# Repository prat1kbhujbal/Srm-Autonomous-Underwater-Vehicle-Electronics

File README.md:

Srm-Autonomous-Underwater-Vehicle-Electronics

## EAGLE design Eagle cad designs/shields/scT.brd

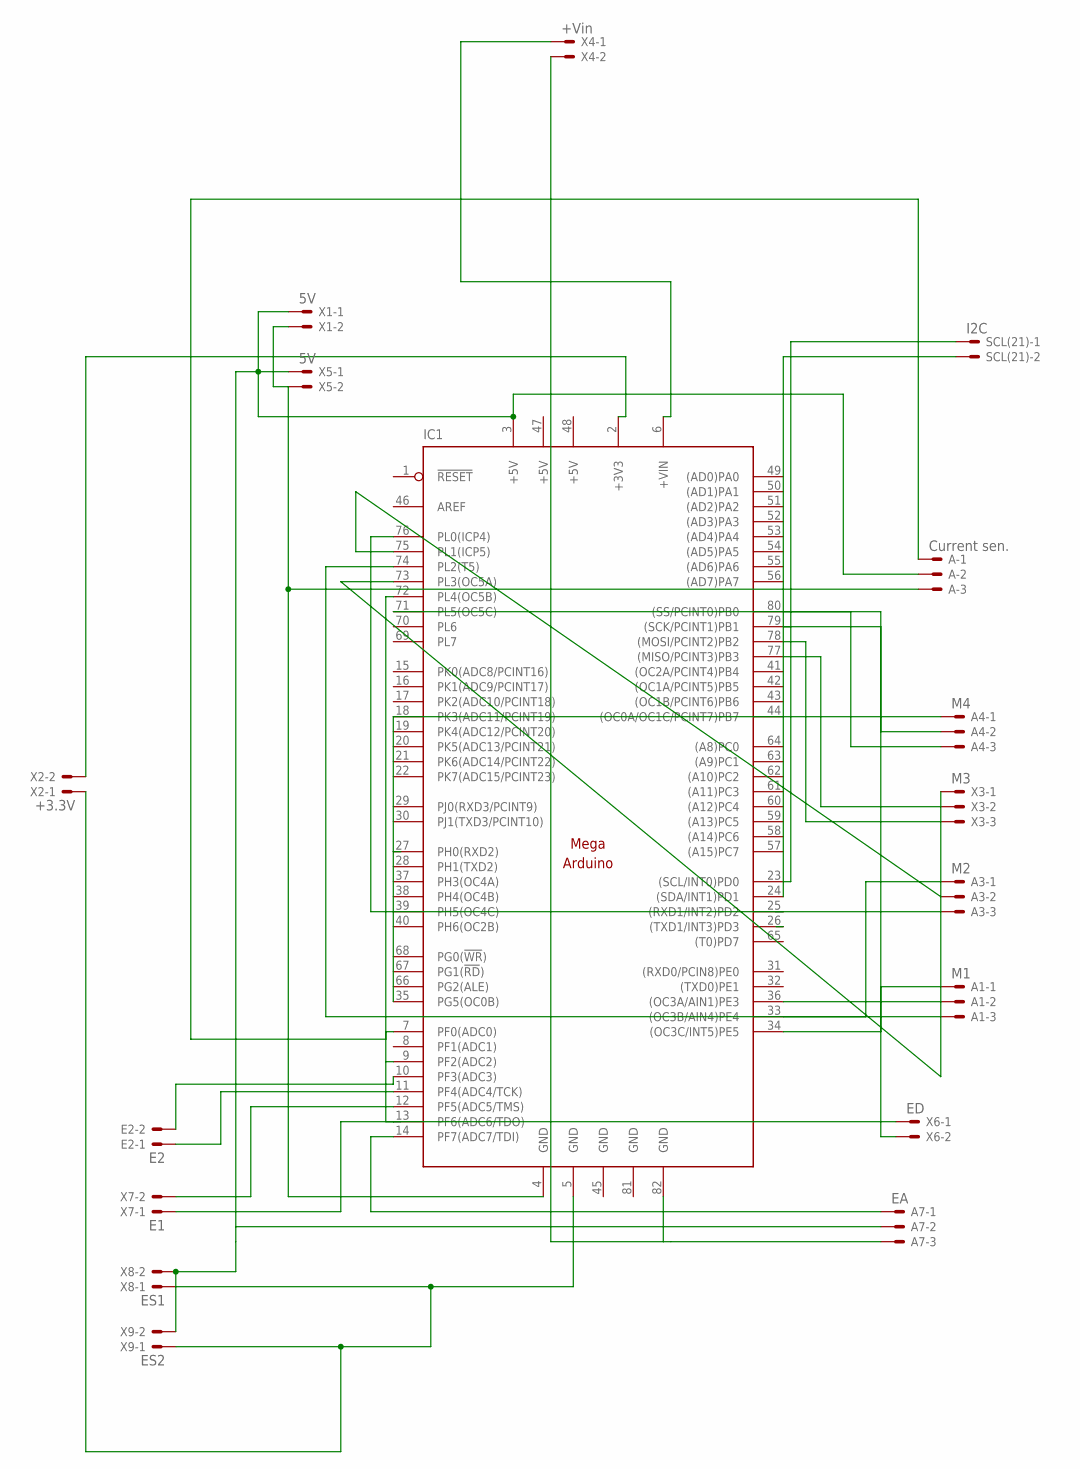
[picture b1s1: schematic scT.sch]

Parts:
A: Current sen.; JST-XH-03-PACKAGE-LONG-PAD
A1: M1; JST-XH-03-PACKAGE-LONG-PAD
A3: M2; JST-XH-03-PACKAGE-LONG-PAD
A4: M4; JST-XH-03-PACKAGE-LONG-PAD
A7: EA; JST-XH-03-PACKAGE-LONG-PAD
E2: E2; JST-XH-02-PACKAGE-LONG-PAD
IC1: MEGAARDUINO_11; MEGA_ARDUINO_1
SCL(21): I2C; JST-XH-02-PACKAGE-LONG-PAD
X1, X5: 5V; JST-XH-02-PACKAGE-LONG-PAD
X2: +3.3V; JST-XH-02-PACKAGE-LONG-PAD
X3: M3; JST-XH-03-PACKAGE-LONG-PAD
X4: +Vin; JST-XH-02-PACKAGE-LONG-PAD
X6: ED; JST-XH-02-PACKAGE-LONG-PAD
X7: E1; JST-XH-02-PACKAGE-LONG-PAD
X8: ES1; JST-XH-02-PACKAGE-LONG-PAD
X9: ES2; JST-XH-02-PACKAGE-LONG-PAD

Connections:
+5V: IC1.47 (+5V), IC1.48 (+5V)
GND: IC1.45 (GND), IC1.81 (GND)
unnamed: IC1.12 (PF5(ADC5/TMS)), X7.2
unnamed: A4.1, IC1.35 (PG5(OC0B))
unnamed: A4.2, IC1.79 ((SCK/PCINT1)PB1)
unnamed: IC1.36 ((OC3A/AIN1)PE3), X3.1
unnamed: A3.2, IC1.75 (PL1(ICP5))
unnamed: A3.1, IC1.33 ((OC3B/AIN4)PE4)
unnamed: A1.1, IC1.34 ((OC3C/INT5)PE5)
unnamed: IC1.77 ((MISO/PCINT3)PB3), X3.2
unnamed: A3.3, IC1.76 (PL0(ICP4))
unnamed: IC1.2 (+3V3), X2.2
unnamed: A.1, IC1.7 (PF0(ADC0))
unnamed: A.3, IC1.4 (GND), X1.2, X5.2
unnamed: A4.3, IC1.80 ((SS/PCINT0)PB0)
unnamed: E2.2, IC1.10 (PF3(ADC3))
unnamed: E2.1, IC1.11 (PF4(ADC4/TCK))
unnamed: IC1.78 ((MOSI/PCINT2)PB2), X3.3
unnamed: IC1.13 (PF6(ADC6/TDO)), X7.1
unnamed: A1.2, IC1.73 (PL3(OC5A))
unnamed: A1.3, IC1.74 (PL2(T5))
unnamed: IC1.5 (GND), X2.1, X8.1, X9.1
unnamed: A.2, A7.2, IC1.3 (+5V), X1.1, X5.1, X8.2, X9.2
unnamed: IC1.72 (PL4(OC5B)), X6.1
unnamed: IC1.71 (PL5(OC5C)), X6.2
unnamed: A7.1, IC1.14 (PF7(ADC7/TDI))
unnamed: A7.3, IC1.82 (GND), X4.2
unnamed: IC1.23 ((SCL/INT0)PD0), SCL(21).1
unnamed: IC1.24 ((SDA/INT1)PD1), SCL(21).2
unnamed: IC1.6 (+VIN), X4.1

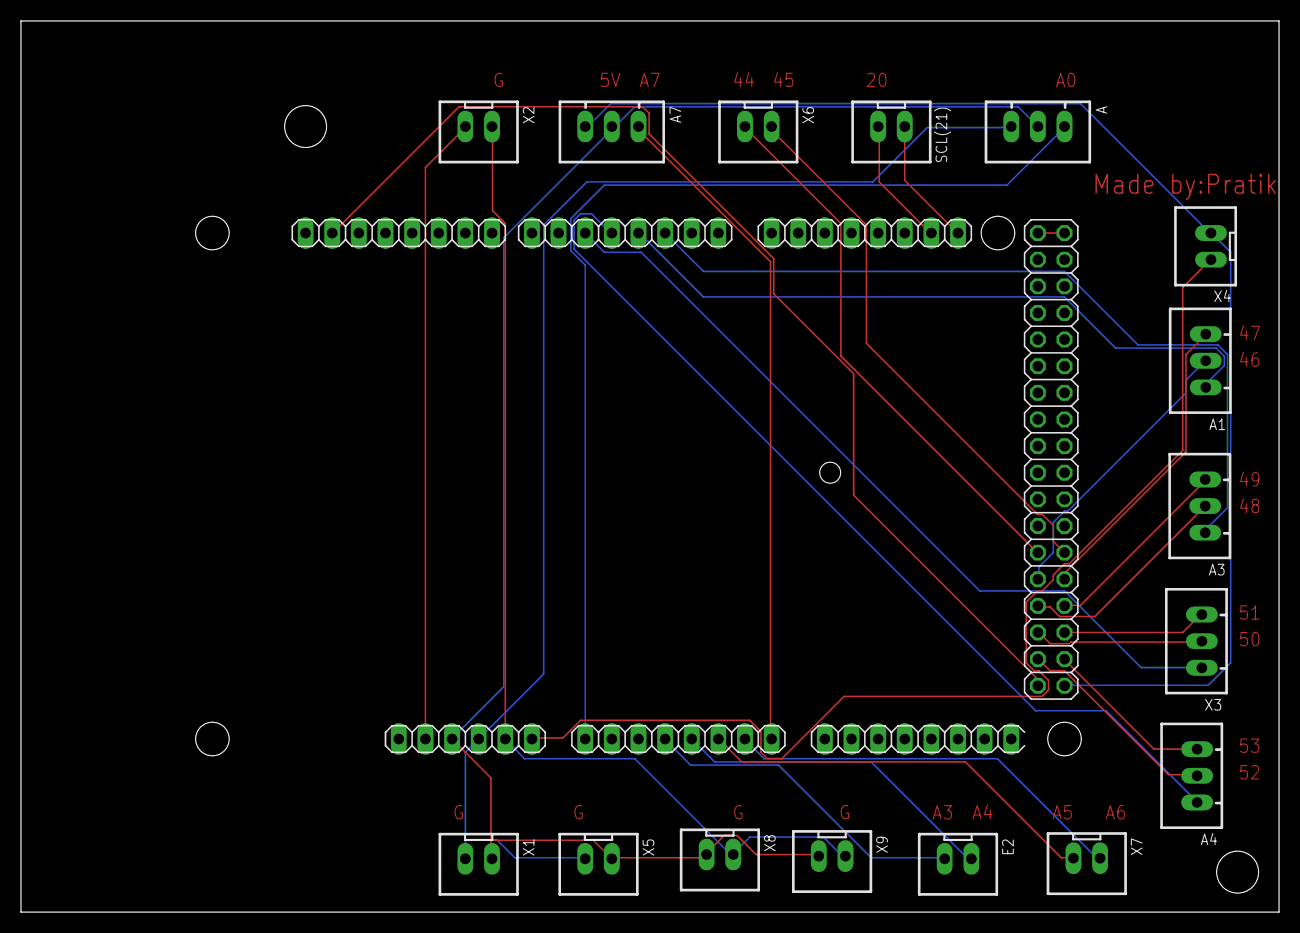
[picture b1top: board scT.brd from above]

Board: 2 copper layers, 120.0 x 85.0 mm, 17 parts (0 on the bottom side), 30 nets.

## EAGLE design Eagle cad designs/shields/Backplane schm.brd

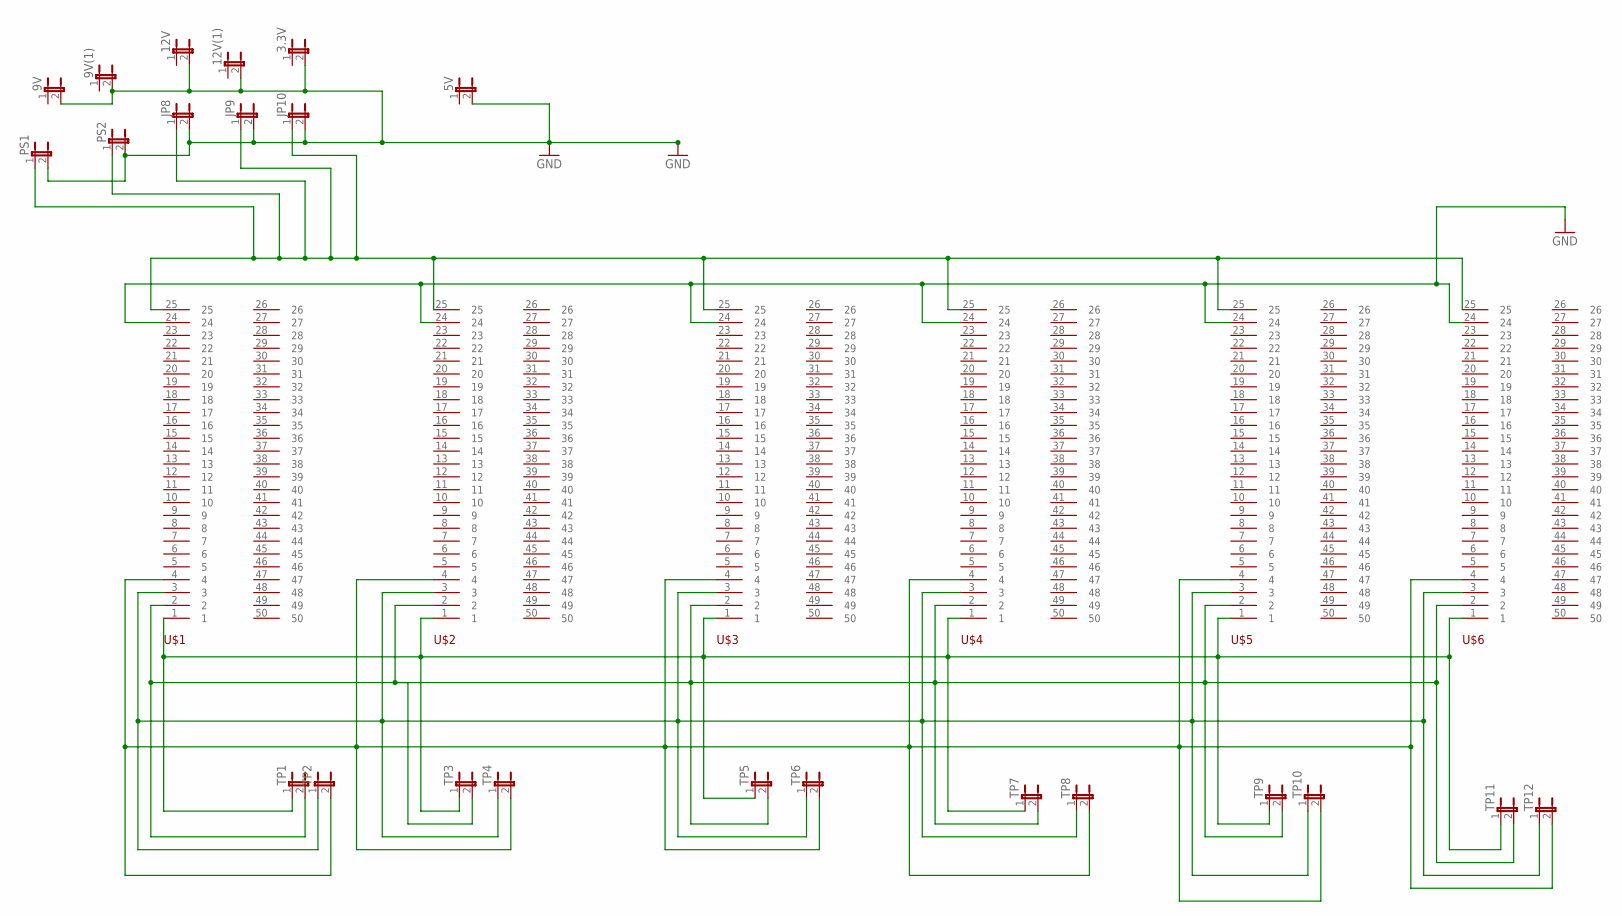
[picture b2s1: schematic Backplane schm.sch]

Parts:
3.3V, 5V, 9V, 9V(1), 12V, 12V(1): JP1E; JP1
JP8, JP9, JP10: JP1E; JP1
PS1, PS2: JP1E; JP1
TP1, TP2, TP3, TP4, TP5, TP6, TP7, TP8, TP9, TP10, TP11, TP12: JP1E; JP1
U$1, U$2, U$3, U$4, U$5, U$6: NG_CD_6364666_D-669581; CON25

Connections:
5: TP1.1, TP3.1, TP5.1, TP7.1, TP9.1, TP11.1, U$1.1, U$2.1, U$3.1, U$4.1, U$5.1, U$6.1
GND: 3.3V.2, 5V.2, 9V.2, 9V(1).2, 12V.2, 12V(1).2, JP8.2, JP9.2, JP10.2, PS1.2, PS2.2, U$1.24, U$2.24, U$3.24, U$4.24, U$5.24, U$6.24
unnamed: TP1.2, TP3.2, TP5.2, TP7.2, TP9.2, TP11.2, U$1.2, U$2.2, U$3.2, U$4.2, U$5.2, U$6.2
unnamed: TP2.1, TP4.1, TP6.1, TP8.1, TP10.1, TP12.1, U$1.3, U$2.3, U$3.3, U$4.3, U$5.3, U$6.3
unnamed: TP2.2, TP4.2, TP6.2, TP8.2, TP10.2, TP12.2, U$1.4, U$2.4, U$3.4, U$4.4, U$5.4, U$6.4
unnamed: JP8.1, JP9.1, JP10.1, PS1.1, PS2.1, U$1.25, U$2.25, U$3.25, U$4.25, U$5.25, U$6.25

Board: 2 copper layers, 29 parts (0 on the bottom side), 6 nets, no tracks yet.

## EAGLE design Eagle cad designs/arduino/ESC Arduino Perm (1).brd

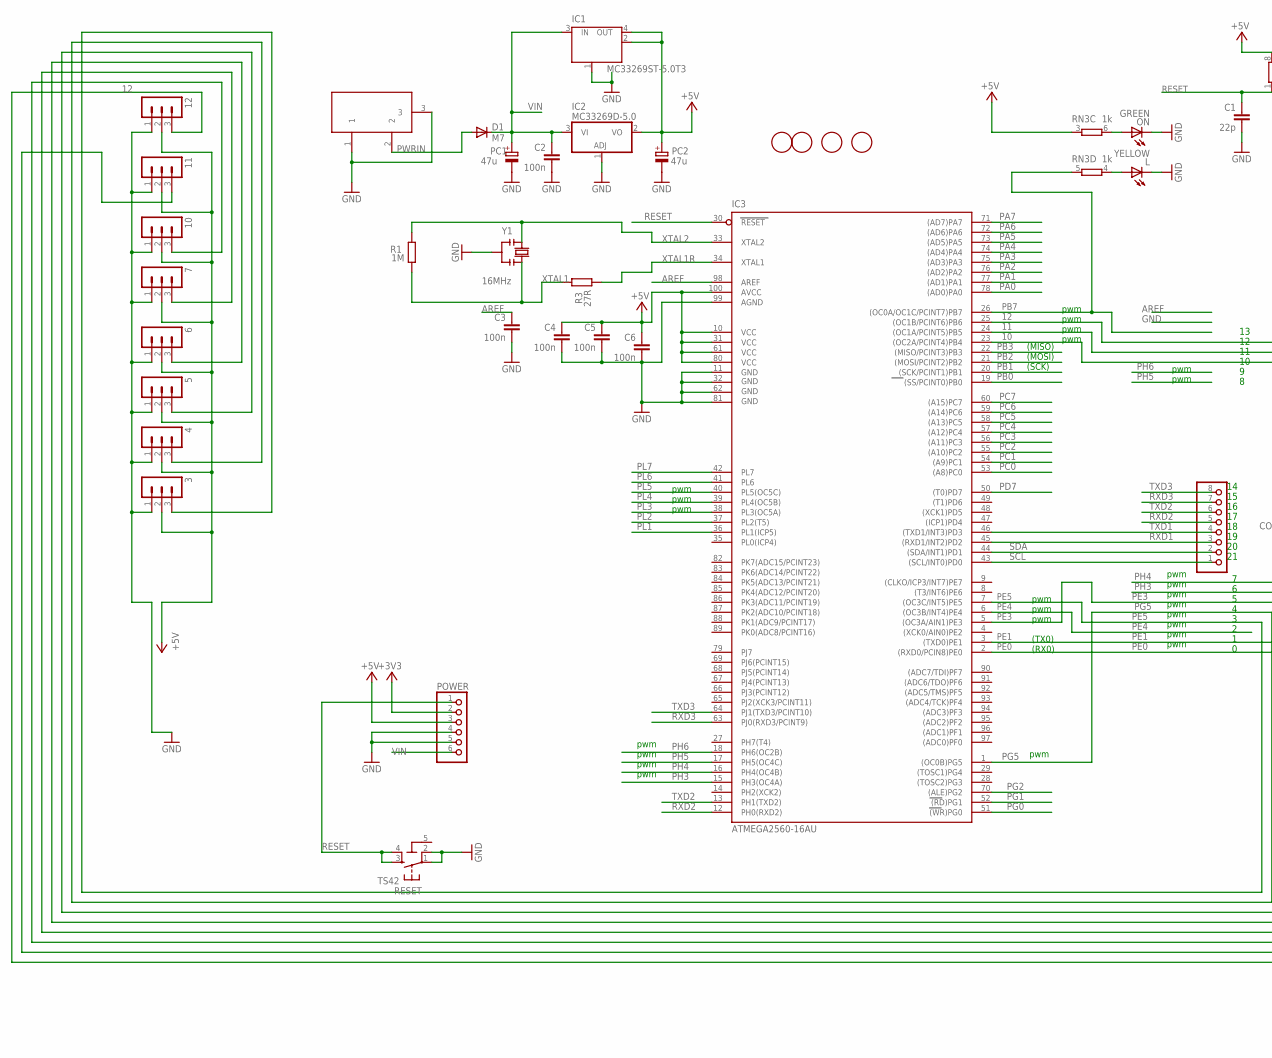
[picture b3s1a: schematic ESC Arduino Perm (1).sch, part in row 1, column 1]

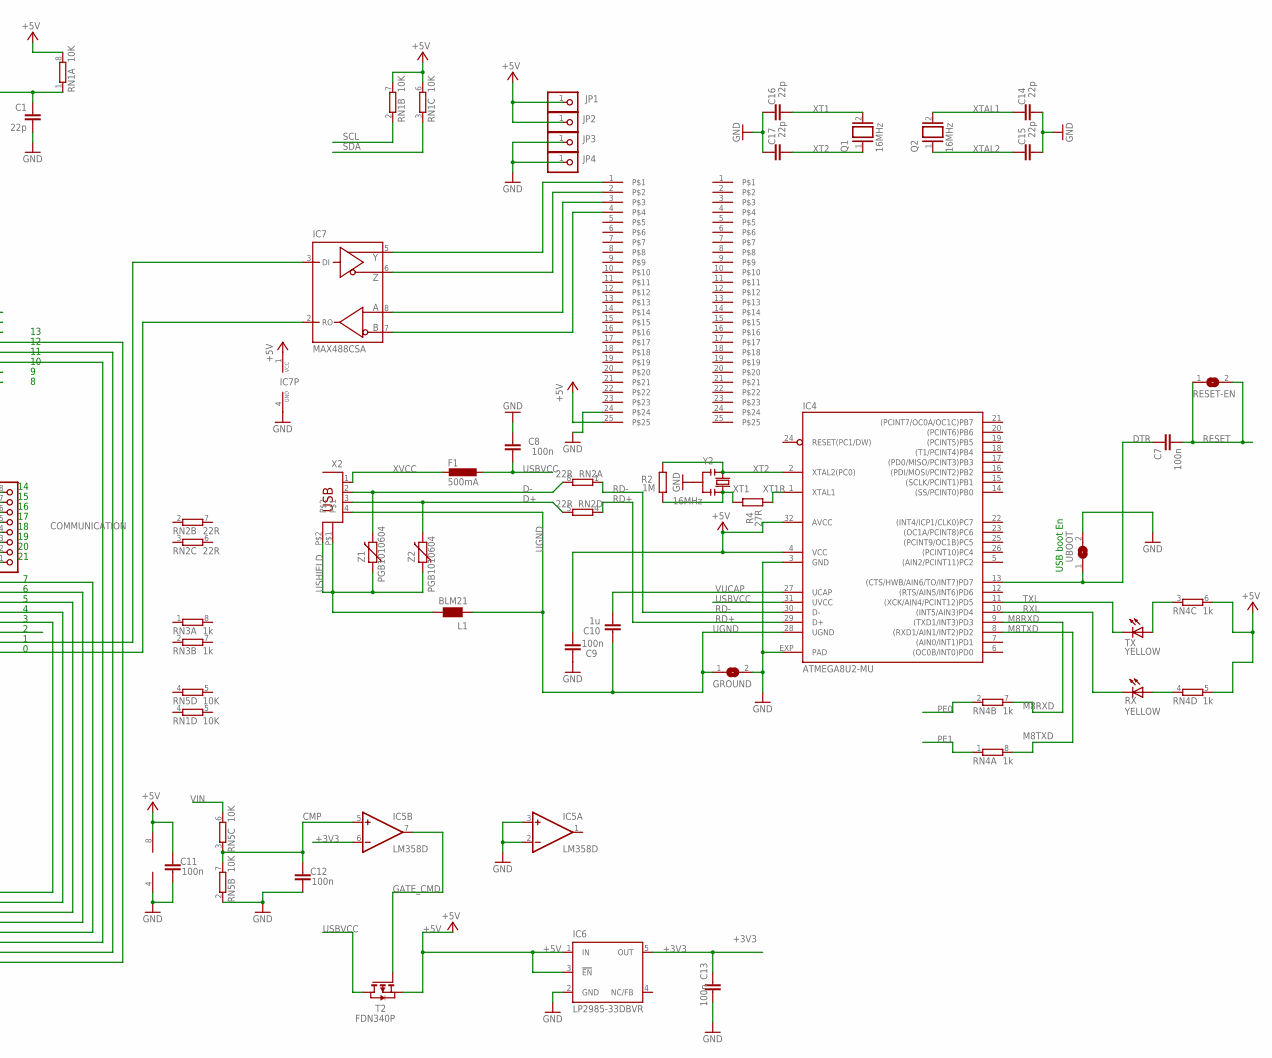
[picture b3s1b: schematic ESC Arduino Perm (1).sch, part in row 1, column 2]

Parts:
3, 4, 5, 6, 7, 10, 11, 12: MA03-1
C1, C14, C15, C16, C17: 22p; C0603-ROUND
C2, C3, C4, C5, C6, C7, C9, C12, C13: 100n; C0603-ROUND
C8, C11: 100n; C0603
C10: 1u; C0603-ROUND
COMMUNICATION: PINHD-1X8; 1X08
D1: M7; SMB
F1: 500mA; L1812
GROUND: SJ
IC1: MC33269ST-5.0T3; SOT223
IC2: MC33269D-5.0; DPACK
IC3: ATMEGA2560-16AU; TQFP100
IC4: ATMEGA8U2-MU; QFN32
IC5: LM358D; SO08
IC6: LP2985-33DBVR; SOT23-DBV
IC7: MAX488CSA; SO08
JP1, JP2, JP3, JP4: PINHD-1X1; 1X01
L: YELLOW; CHIP-LED0805
L1: BLM21; 0805
ON: GREEN; CHIP-LED0805
PC1, PC2: 47u; PANASONIC_D
POWER: PINHD-1X6; 1X06
Q1, Q2: 16MHz; QS
R1, R2: 1M; R0603-ROUND
R3, R4: 27R; R0603-ROUND
RESET: TS42
RESET-EN: SJ
RN1, RN5: 10K; CAT16
RN2: 22R; CAY16
RN3, RN4: 1k; CAY16
RX: YELLOW; CHIP-LED0805
T2: FDN340P; SOT-23
TX: YELLOW; CHIP-LED0805
U$1, U$6: CARD-EDGE-LINEAR-ZIF; CARD-EDGE
U$2, U$3, U$4, U$5: FIDUCIALMOUNT; FIDUCIA-MOUNT
UBOOT: SJ
X1: DC21MMX; DC-21MM
X2: PN61729
Y1, Y2: 16MHz; RESONATOR
Z1, Z2: PGB1010604; CT/CN0603

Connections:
5-GND: RESET.5 (5-GND)
10: 10.3, IC3.23 ((OC2A/PCINT4)PB4)
11: 11.3, IC3.24 ((OC1A/PCINT5)PB5)
12: 12.3, IC3.25 ((OC1B/PCINT6)PB6)
+3V3: C13.2, IC5.6 (-IN), IC6.5 (OUT), POWER.2
+5V: 3.2, 4.2, 5.2, 6.2, 7.2, 10.2, 11.2, 12.2, C4.1, C5.1, C6.1, C9.1, C11.2, IC1.2 (OUT), IC1.4 (OUT), IC2.2 (VO), IC3.10 (VCC), IC3.31 (VCC1), IC3.61 (VCC2), IC3.80 (VCC3), IC3.100 (AVCC), IC4.4 (VCC), IC4.32 (AVCC), IC5.8 (V+), IC6.1 (IN), IC6.3 (!EN), IC7.1 (VCC), JP1.1, JP2.1, PC2.+, POWER.3, RN1.6 (2), RN1.7 (2), RN1.8 (2), RN3.3 (1), RN4.5 (2), RN4.6 (2), T2.2 (S), U$1.25
AREF: C3.1, IC3.98 (AREF)
CMP: C12.2, IC5.5 (+IN), RN5.3 (1), RN5.7 (2)
D+: RN2.5 (2), X2.3, Z2.2
D-: RN2.8 (2), X2.2, Z1.2
DTR: C7.1, IC4.13 ((CTS/HWB/AIN6/TO/INT7)PD7), UBOOT.1
GATE_CMD: IC5.7 (OUT), T2.3 (G)
GND: 3.1, 4.1, 5.1, 6.1, 7.1, 10.1, 11.1, 12.1, C1.2, C2.2, C3.2, C4.2, C5.2, C6.2, C8.2, C9.2, C11.1, C12.1, C13.1, C14.1, C15.1, C16.2, C17.2, GROUND.2, IC1.1 (GND/ADJ), IC2.1 (ADJ), IC3.11 (GND), IC3.32 (GND1), IC3.62 (GND2), IC3.81 (GND3), IC3.99 (AGND), IC4.3 (GND), IC4.EXP (PAD), IC5.2 (-IN), IC5.3 (+IN), IC5.4 (V-), IC6.2 (GND), IC7.4 (GND), JP3.1, JP4.1, L.C, ON.C, PC1.-, PC2.-, POWER.4, POWER.5, RESET.1, RESET.2, RN5.2 (1), U$1.24, UBOOT.2, X1.1, X1.3, Y1.2, Y2.2
M8RXD: IC4.9 ((TXD1/INT3)PD3), RN4.7 (2)
M8TXD: IC4.8 ((RXD1/AIN1/INT2)PD2), RN4.8 (2)
unnamed: L.A, RN3.4 (1)
unnamed: ON.A, RN3.6 (2)
unnamed: IC7.5 (Y), U$1.1
unnamed: IC7.6 (Z), U$1.2
unnamed: IC7.8 (A), U$1.3
unnamed: IC7.7 (B), U$1.4
unnamed: RN4.4 (1), RX.A
unnamed: RN4.3 (1), TX.A
PA0: IC3.78 ((AD0)PA0)
PA1: IC3.77 ((AD1)PA1)
PA2: IC3.76 ((AD2)PA2)
PA3: IC3.75 ((AD3)PA3)
PA4: IC3.74 ((AD4)PA4)
PA5: IC3.73 ((AD5)PA5)
PA6: IC3.72 ((AD6)PA6)
PA7: IC3.71 ((AD7)PA7)
PB0: IC3.19 ((SS/PCINT0)PB0)
PB1: IC3.20 ((SCK/PCINT1)PB1)
PB2: IC3.21 ((MOSI/PCINT2)PB2)
PB3: IC3.22 ((MISO/PCINT3)PB3)
PB7: IC3.26 ((OC0A/OC1C/PCINT7)PB7), RN3.5 (2)
PC0: IC3.53 ((A8)PC0)
PC1: IC3.54 ((A9)PC1)
PC2: IC3.55 ((A10)PC2)
PC3: IC3.56 ((A11)PC3)
PC4: IC3.57 ((A12)PC4)
PC5: IC3.58 ((A13)PC5)
PC6: IC3.59 ((A14)PC6)
PC7: IC3.60 ((A15)PC7)
PD7: IC3.50 ((T0)PD7)
PE0: IC3.2 ((RXD0/PCIN8)PE0), IC7.2 (RO), RN4.2 (1)
PE1: IC3.3 ((TXD0)PE1), IC7.3 (DI), RN4.1
PE3: 5.3, IC3.5 ((OC3A/AIN1)PE3)
PE4: IC3.6 ((OC3B/INT4)PE4)
PE5: 3.3, IC3.7 ((OC3C/INT5)PE5)
PG0: IC3.51 ((WR)PG0)
PG1: IC3.52 ((RD)PG1)
PG2: IC3.70 ((ALE)PG2)
PG5: 4.3, IC3.1 ((OC0B)PG5)
PH3: 6.3, IC3.15 (PH3(OC4A))
PH4: 7.3, IC3.16 (PH4(OC4B))
PH5: IC3.17 (PH5(OC4C))
PH6: IC3.18 (PH6(OC2B))
PL1: IC3.36 (PL1(ICP5))
PL2: IC3.37 (PL2(T5))
PL3: IC3.38 (PL3(OC5A))
PL4: IC3.39 (PL4(OC5B))
PL5: IC3.40 (PL5(OC5C))
PL6: IC3.41 (PL6)
PL7: IC3.42 (PL7)
PWRIN: D1.A, X1.2
RD+: IC4.29 (D+), RN2.4 (1)
RD-: IC4.30 (D-), RN2.1
RESET: C1.1, C7.2, IC3.30 (RESET), POWER.1, RESET.3, RESET.4, RESET-EN.1, RESET-EN.2, RN1.1
RXD1: COMMUNICATION.3, IC3.45 ((RXD1/INT2)PD2)
RXD2: COMMUNICATION.5, IC3.12 (PH0(RXD2))
RXD3: COMMUNICATION.7, IC3.63 (PJ0(RXD3/PCINT9))
RXL: IC4.10 ((INT5/AIN3)PD4), RX.C
SCL: COMMUNICATION.1, IC3.43 ((SCL/INT0)PD0), RN1.2 (1)
SDA: COMMUNICATION.2, IC3.44 ((SDA/INT1)PD1), RN1.3 (1)
TXD1: COMMUNICATION.4, IC3.46 ((TXD1/INT3)PD3)
TXD2: COMMUNICATION.6, IC3.13 (PH1(TXD2))
TXD3: COMMUNICATION.8, IC3.64 (PJ1(TXD3/PCINT10))
TXL: IC4.11 ((XCK/AIN4/PCINT12)PD5), TX.C
UGND: C10.2, GROUND.1, IC4.28 (UGND), L1.1, X2.4
USBVCC: C8.1, F1.1, IC4.31 (UVCC), T2.1 (D)
USHIELD: L1.2, X2.P$1, X2.P$2, Z1.1, Z2.1
VIN: C2.1, D1.C, IC1.3 (IN), IC2.3 (VI), PC1.+, POWER.6, RN5.6 (2)
VUCAP: C10.1, IC4.27 (UCAP)
XT1: C16.1, Q1.2, R2.1, R4.2, Y2.3
XT1R: IC4.1 (XTAL1), R4.1
XT2: C17.1, IC4.2 (XTAL2(PC0)), Q1.1, R2.2, Y2.1
XTAL1: C14.2, Q2.2, R1.1, R3.2, Y1.3
XTAL1R: IC3.34 (XTAL1), R3.1
XTAL2: C15.2, IC3.33 (XTAL2), Q2.1, R1.2, Y1.1
XVCC: F1.2, X2.1

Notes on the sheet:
pwm
(TX0)
(RX0)
(MISO)
(SCK)
(MOSI)
USB boot En

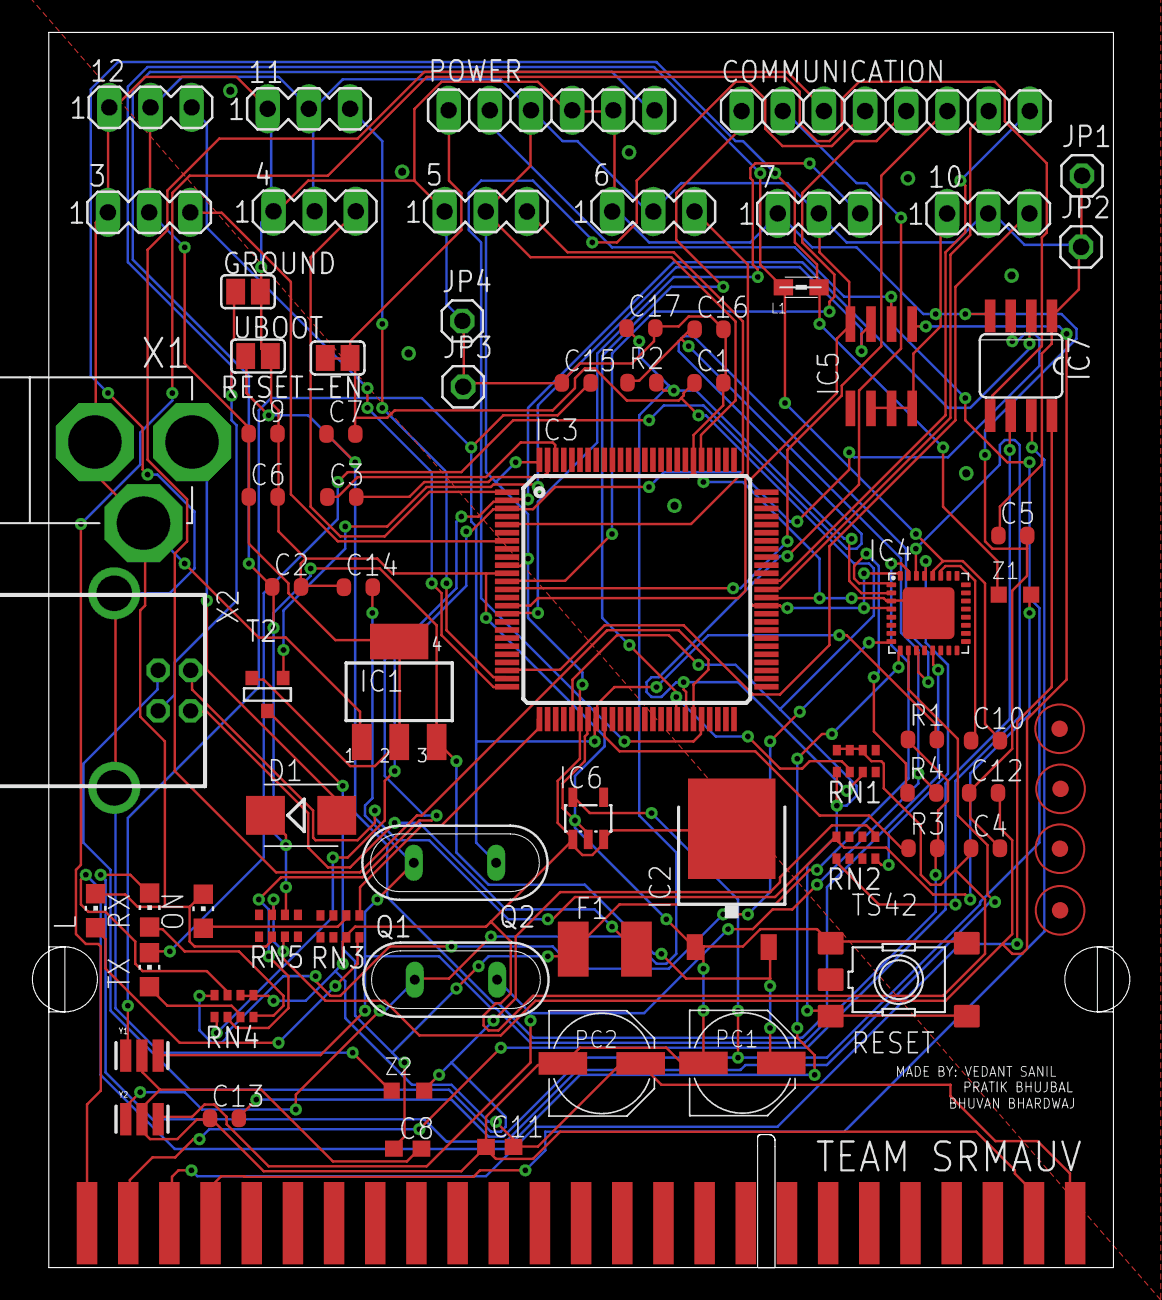
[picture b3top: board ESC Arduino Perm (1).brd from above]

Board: 2 copper layers, 67.7 x 76.2 mm, 75 parts (1 on the bottom side), 56 nets.

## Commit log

2019-11-15 SrmAuv Electronics
